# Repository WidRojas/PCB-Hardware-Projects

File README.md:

## [Variable Buck Converter(WIP)](./Buck/)

This project involved creating a buck converter which could regulate a 10V power supply to voltage suitable for a breadboard. simulations were done in LTspice and KiCad was used for creating schematics and PCB Layout.

### PCB Revision #1

*Currently awaiting second revision, due to high currents causing gate driver IC to fry*

## [LED Matrix](./Audio_Matrix/)

This project involved the creation of a LED matrix to be used in conjunction with audio [visualizer software](https://github.com/WidRojas/Audio_Visualiser), LED's are charlieplexed, STM32C071RBT6 was selected due to relatively low cost.

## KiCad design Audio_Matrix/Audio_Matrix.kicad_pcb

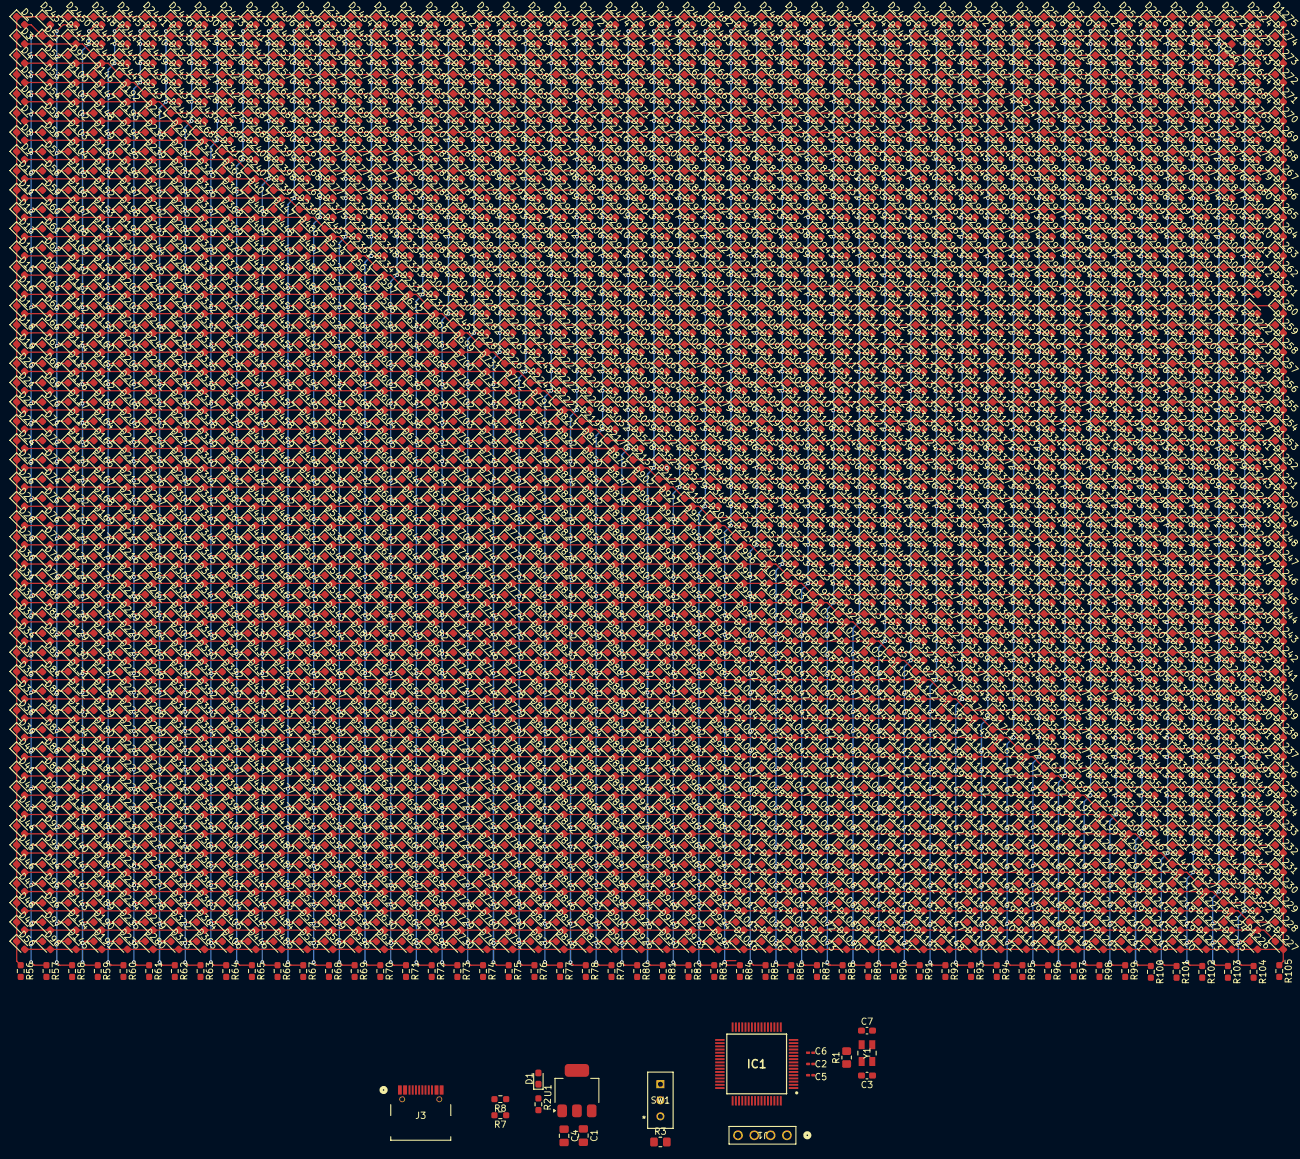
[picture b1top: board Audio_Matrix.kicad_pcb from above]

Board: 2 copper layers, 2519 parts (0 on the bottom side), 111 nets.

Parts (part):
C1, C4: 22u; C_0805_2012Metric_Pad1.18x1.45mm_HandSolder
C2, C5, C6: 100n; C_0201_0603Metric_Pad0.64x0.40mm_HandSolder
C3, C7: 10p; C_0603_1608Metric_Pad1.08x0.95mm_HandSolder
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
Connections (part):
+3.3V: C2.1, C4.1, C5.1, D1.2 (A), IC1.7 (VREF+), IC1.8 (VDD/VDDA), J1.4, SW1.1 (C), U1.2 (VO)
/CLK_IN: C3.1, IC1.10 (PF0-OSC_IN), Y1.1
/CLK_OUT: IC1.11 (PF1-OSC_OUT), R1.1
/LS1: D2.1 (K), D3.1 (K), D4.1 (K), D5.1 (K), D6.1 (K), D7.1 (K), D8.1 (K), D9.1 (K), D10.1 (K), D11.1 (K), D12.1 (K), D13.1 (K), D14.1 (K), D15.1 (K), D16.1 (K), D17.1 (K), D18.1 (K), D19.1 (K), D20.1 (K), D21.1 (K), D22.1 (K), D23.1 (K), D24.1 (K), D25.1 (K), D26.1 (K), D27.1 (K), D28.1 (K), D29.1 (K), D30.1 (K), D31.1 (K), D32.1 (K), D33.1 (K), D34.1 (K), D35.1 (K), D36.1 (K), D37.1 (K), D38.1 (K), D39.1 (K), D40.1 (K), D41.1 (K), D42.1 (K), D43.1 (K), D44.1 (K), D45.1 (K), D46.1 (K), D47.1 (K), D48.1 (K), D49.1 (K), D50.1 (K), D1275.1 (K), D2385.1 (K), D2396.1 (K), D2406.1 (K), D2415.1 (K), D2423.1 (K), D2430.1 (K), D2436.1 (K), D2441.1 (K), D2445.1 (K), D2448.1 (K), D2450.1 (K), D2451.1 (K), D2454.1 (K), D2456.1 (K), D2458.1 (K), D2460.1 (K), D2462.1 (K), D2464.1 (K), D2466.1 (K), D2468.1 (K), D2470.1 (K), D2472.1 (K), D2474.1 (K), D2476.1 (K), D2478.1 (K), D2480.1 (K), D2482.1 (K), D2484.1 (K), D2486.1 (K), D2488.1 (K), D2490.1 (K)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
/LS2: D2.2 (A), D51.1 (K), D52.1 (K), D53.1 (K), D54.1 (K), D55.1 (K), D56.1 (K), D57.1 (K), D58.1 (K), D59.1 (K), D60.1 (K), D61.1 (K), D62.1 (K), D63.1 (K), D64.1 (K), D65.1 (K), D66.1 (K), D67.1 (K), D68.1 (K), D69.1 (K), D70.1 (K), D71.1 (K), D72.1 (K), D73.1 (K), D74.1 (K), D75.1 (K), D76.1 (K), D77.1 (K), D78.1 (K), D79.1 (K), D80.1 (K), D81.1 (K), D82.1 (K), D83.1 (K), D84.1 (K), D85.1 (K), D86.1 (K), D87.1 (K), D88.1 (K), D89.1 (K), D90.1 (K), D91.1 (K), D92.1 (K), D93.1 (K), D94.1 (K), D95.1 (K), D96.1 (K), D97.1 (K), D98.1 (K), D1274.1 (K), D2384.1 (K), D2395.1 (K), D2405.1 (K), D2414.1 (K), D2422.1 (K), D2429.1 (K), D2435.1 (K), D2440.1 (K), D2444.1 (K), D2447.1 (K), D2449.1 (K), D2451.2 (A), D2455.1 (K), D2457.1 (K), D2459.1 (K), D2461.1 (K), D2463.1 (K), D2465.1 (K), D2467.1 (K), D2469.1 (K), D2471.1 (K), D2473.1 (K), D2475.1 (K), D2477.1 (K), D2479.1 (K), D2481.1 (K), D2483.1 (K), D2485.1 (K), D2487.1 (K), D2489.1 (K), D2491.1 (K)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
/LS3: D3.2 (A), D51.2 (A), D99.1 (K), D100.1 (K), D101.1 (K), D102.1 (K), D103.1 (K), D104.1 (K), D105.1 (K), D106.1 (K), D107.1 (K), D108.1 (K), D109.1 (K), D110.1 (K), D111.1 (K), D112.1 (K), D113.1 (K), D114.1 (K), D115.1 (K), D116.1 (K), D117.1 (K), D118.1 (K), D119.1 (K), D120.1 (K), D121.1 (K), D122.1 (K), D123.1 (K), D124.1 (K), D125.1 (K), D126.1 (K), D127.1 (K), D128.1 (K), D129.1 (K), D130.1 (K), D131.1 (K), D132.1 (K), D133.1 (K), D134.1 (K), D135.1 (K), D136.1 (K), D137.1 (K), D138.1 (K), D139.1 (K), D140.1 (K), D141.1 (K), D142.1 (K), D143.1 (K), D144.1 (K), D145.1 (K), D1273.1 (K), D2393.1 (K), D2421.1 (K), D2439.1 (K), D2443.1 (K), D2446.1 (K), D2449.2 (A), D2450.2 (A), D2526.1 (K), D2527.1 (K), D2528.1 (K), D2530.1 (K), D2531.1 (K), D2537.1 (K), D2538.1 (K), D2541.1 (K), D2544.1 (K), D2545.1 (K), D2546.1 (K), D2549.1 (K), D2550.1 (K), D2551.1 (K), D2553.1 (K), D2558.1 (K), D2560.1 (K), D2562.1 (K), D2566.1 (K), D2567.1 (K), D2573.1 (K), D2575.1 (K), D2577.1 (K), D2579.1 (K)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
/LS4: D4.2 (A), D52.2 (A), D99.2 (A), D146.1 (K), D147.1 (K), D148.1 (K), D149.1 (K), D150.1 (K), D151.1 (K), D152.1 (K), D153.1 (K), D154.1 (K), D155.1 (K), D156.1 (K), D157.1 (K), D158.1 (K), D159.1 (K), D160.1 (K), D161.1 (K), D162.1 (K), D163.1 (K), D164.1 (K), D165.1 (K), D166.1 (K), D167.1 (K), D168.1 (K), D169.1 (K), D170.1 (K), D171.1 (K), D172.1 (K), D173.1 (K), D174.1 (K), D175.1 (K), D176.1 (K), D177.1 (K), D178.1 (K), D179.1 (K), D180.1 (K), D181.1 (K), D182.1 (K), D183.1 (K), D184.1 (K), D185.1 (K), D186.1 (K), D187.1 (K), D188.1 (K), D189.1 (K), D190.1 (K), D191.1 (K), D1272.1 (K), D2420.1 (K), D2427.1 (K), D2433.1 (K), D2438.1 (K), D2442.1 (K), D2446.2 (A), D2447.2 (A), D2448.2 (A), D2569.1 (K), D2570.1 (K), D2571.1 (K), D2572.1 (K), D2574.1 (K), D2576.1 (K), D2578.1 (K), D2580.1 (K), D2582.1 (K), D2584.1 (K), D2586.1 (K), D2588.1 (K), D2590.1 (K), D2592.1 (K), D2594.1 (K), D2596.1 (K), D2598.1 (K), D2600.1 (K), D2602.1 (K), D2604.1 (K), D2606.1 (K), D2608.1 (K), D2610.1 (K)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
/LS5: D5.2 (A), D53.2 (A), D100.2 (A), D146.2 (A), D192.1 (K), D193.1 (K), D194.1 (K), D195.1 (K), D196.1 (K), D197.1 (K), D198.1 (K), D199.1 (K), D200.1 (K), D201.1 (K), D202.1 (K), D203.1 (K), D204.1 (K), D205.1 (K), D206.1 (K), D207.1 (K), D208.1 (K), D209.1 (K), D210.1 (K), D211.1 (K), D212.1 (K), D213.1 (K), D214.1 (K), D215.1 (K), D216.1 (K), D217.1 (K), D218.1 (K), D219.1 (K), D220.1 (K), D221.1 (K), D222.1 (K), D223.1 (K), D224.1 (K), D225.1 (K), D226.1 (K), D227.1 (K), D228.1 (K), D229.1 (K), D230.1 (K), D231.1 (K), D232.1 (K), D233.1 (K), D234.1 (K), D235.1 (K), D236.1 (K), D1271.1 (K), D2426.1 (K), D2428.1 (K), D2432.1 (K), D2437.1 (K), D2442.2 (A), D2443.2 (A), D2444.2 (A), D2445.2 (A), D2645.1 (K), D2646.1 (K), D2647.1 (K), D2648.1 (K), D2649.1 (K), D2650.1 (K), D2651.1 (K), D2652.1 (K), D2653.1 (K), D2654.1 (K), D2655.1 (K), D2656.1 (K), D2657.1 (K), D2658.1 (K), D2659.1 (K), D2660.1 (K), D2661.1 (K), D2662.1 (K), D2663.1 (K), D2664.1 (K), D2665.1 (K), D2666.1 (K), D2667.1 (K)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
/LS6: D6.2 (A), D54.2 (A), D101.2 (A), D147.2 (A), D192.2 (A), D237.1 (K), D238.1 (K), D239.1 (K), D240.1 (K), D241.1 (K), D242.1 (K), D243.1 (K), D244.1 (K), D245.1 (K), D246.1 (K), D247.1 (K), D248.1 (K), D249.1 (K), D250.1 (K), D251.1 (K), D252.1 (K), D253.1 (K), D254.1 (K), D255.1 (K), D256.1 (K), D257.1 (K), D258.1 (K), D259.1 (K), D260.1 (K), D261.1 (K), D262.1 (K), D263.1 (K), D264.1 (K), D265.1 (K), D266.1 (K), D267.1 (K), D268.1 (K), D269.1 (K), D270.1 (K), D271.1 (K), D272.1 (K), D273.1 (K), D274.1 (K), D275.1 (K), D276.1 (K), D277.1 (K), D278.1 (K), D279.1 (K), D280.1 (K), D1270.1 (K), D2424.1 (K), D2431.1 (K), D2434.1 (K), D2437.2 (A), D2438.2 (A), D2439.2 (A), D2440.2 (A), D2441.2 (A), D2687.1 (K), D2689.1 (K), D2691.1 (K), D2693.1 (K), D2695.1 (K), D2697.1 (K), D2699.1 (K), D2701.1 (K), D2703.1 (K), D2705.1 (K), D2707.1 (K), D2709.1 (K), D2711.1 (K), D2713.1 (K), D2715.1 (K), D2717.1 (K), D2719.1 (K), D2721.1 (K), D2723.1 (K), D2725.1 (K), D2727.1 (K), D2729.1 (K), D2731.1 (K)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
/LS7: D7.2 (A), D55.2 (A), D102.2 (A), D148.2 (A), D193.2 (A), D237.2 (A), D281.1 (K), D282.1 (K), D283.1 (K), D284.1 (K), D285.1 (K), D286.1 (K), D287.1 (K), D288.1 (K), D289.1 (K), D290.1 (K), D291.1 (K), D292.1 (K), D293.1 (K), D294.1 (K), D295.1 (K), D296.1 (K), D297.1 (K), D298.1 (K), D299.1 (K), D300.1 (K), D301.1 (K), D302.1 (K), D303.1 (K), D304.1 (K), D305.1 (K), D306.1 (K), D307.1 (K), D308.1 (K), D309.1 (K), D310.1 (K), D311.1 (K), D312.1 (K), D313.1 (K), D314.1 (K), D315.1 (K), D316.1 (K), D317.1 (K), D318.1 (K), D319.1 (K), D320.1 (K), D321.1 (K), D322.1 (K), D323.1 (K), D1269.1 (K), D2431.2 (A), D2432.2 (A), D2433.2 (A), D2435.2 (A), D2436.2 (A), D2526.2 (A), D2685.1 (K), D2686.1 (K), D2688.1 (K), D2690.1 (K), D2692.1 (K), D2694.1 (K), D2696.1 (K), D2698.1 (K), D2700.1 (K), D2702.1 (K), D2704.1 (K), D2706.1 (K), D2708.1 (K), D2710.1 (K), D2712.1 (K), D2714.1 (K), D2716.1 (K), D2718.1 (K), D2720.1 (K), D2722.1 (K), D2724.1 (K), D2726.1 (K), D2728.1 (K), D2730.1 (K), D2732.1 (K)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
/LS8: D8.2 (A), D56.2 (A), D103.2 (A), D149.2 (A), D194.2 (A), D238.2 (A), D281.2 (A), D324.1 (K), D325.1 (K), D326.1 (K), D327.1 (K), D328.1 (K), D329.1 (K), D330.1 (K), D331.1 (K), D332.1 (K), D333.1 (K), D334.1 (K), D335.1 (K), D336.1 (K), D337.1 (K), D338.1 (K), D339.1 (K), D340.1 (K), D341.1 (K), D342.1 (K), D343.1 (K), D344.1 (K), D345.1 (K), D346.1 (K), D347.1 (K), D348.1 (K), D349.1 (K), D350.1 (K), D351.1 (K), D352.1 (K), D353.1 (K), D354.1 (K), D355.1 (K), D356.1 (K), D357.1 (K), D358.1 (K), D359.1 (K), D360.1 (K), D361.1 (K), D362.1 (K), D363.1 (K), D364.1 (K), D365.1 (K), D1268.1 (K), D2399.1 (K), D2408.1 (K), D2416.1 (K), D2427.2 (A), D2428.2 (A), D2429.2 (A), D2430.2 (A), D2434.2 (A), D2527.2 (A), D2685.2 (A), D2767.1 (K), D2770.1 (K), D2773.1 (K), D2776.1 (K), D2779.1 (K), D2782.1 (K), D2785.1 (K), D2788.1 (K), D2791.1 (K), D2794.1 (K), D2797.1 (K), D2800.1 (K), D2803.1 (K), D2806.1 (K), D2809.1 (K), D2812.1 (K), D2815.1 (K), D2818.1 (K), D2821.1 (K), D2824.1 (K), D2827.1 (K)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
/LS9: D9.2 (A), D57.2 (A), D104.2 (A), D150.2 (A), D195.2 (A), D239.2 (A), D282.2 (A), D324.2 (A), D366.1 (K), D367.1 (K), D368.1 (K), D369.1 (K), D370.1 (K), D371.1 (K), D372.1 (K), D373.1 (K), D374.1 (K), D375.1 (K), D376.1 (K), D377.1 (K), D378.1 (K), D379.1 (K), D380.1 (K), D381.1 (K), D382.1 (K), D383.1 (K), D384.1 (K), D385.1 (K), D386.1 (K), D387.1 (K), D388.1 (K), D389.1 (K), D390.1 (K), D391.1 (K), D392.1 (K), D393.1 (K), D394.1 (K), D395.1 (K), D396.1 (K), D397.1 (K), D398.1 (K), D399.1 (K), D400.1 (K), D401.1 (K), D402.1 (K), D403.1 (K), D404.1 (K), D405.1 (K), D406.1 (K), D1267.1 (K), D2398.1 (K), D2407.1 (K), D2416.2 (A), D2420.2 (A), D2422.2 (A), D2423.2 (A), D2424.2 (A), D2426.2 (A), D2528.2 (A), D2686.2 (A), D2768.1 (K), D2771.1 (K), D2774.1 (K), D2777.1 (K), D2780.1 (K), D2783.1 (K), D2786.1 (K), D2789.1 (K), D2792.1 (K), D2795.1 (K), D2798.1 (K), D2801.1 (K), D2804.1 (K), D2807.1 (K), D2810.1 (K), D2813.1 (K), D2816.1 (K), D2819.1 (K), D2822.1 (K), D2825.1 (K), D2828.1 (K)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
/LS10: D10.2 (A), D58.2 (A), D105.2 (A), D151.2 (A), D196.2 (A), D240.2 (A), D283.2 (A), D325.2 (A), D366.2 (A), D407.1 (K), D408.1 (K), D409.1 (K), D410.1 (K), D411.1 (K), D412.1 (K), D413.1 (K), D414.1 (K), D415.1 (K), D416.1 (K), D417.1 (K), D418.1 (K), D419.1 (K), D420.1 (K), D421.1 (K), D422.1 (K), D423.1 (K), D424.1 (K), D425.1 (K), D426.1 (K), D427.1 (K), D428.1 (K), D429.1 (K), D430.1 (K), D431.1 (K), D432.1 (K), D433.1 (K), D434.1 (K), D435.1 (K), D436.1 (K), D437.1 (K), D438.1 (K), D439.1 (K), D440.1 (K), D441.1 (K), D442.1 (K), D443.1 (K), D444.1 (K), D445.1 (K), D446.1 (K), D1266.1 (K), D2397.1 (K), D2407.2 (A), D2408.2 (A), D2414.2 (A), D2415.2 (A), D2421.2 (A), D2569.2 (A), D2645.2 (A), D2687.2 (A), D2688.2 (A), D2769.1 (K), D2772.1 (K), D2775.1 (K), D2778.1 (K), D2781.1 (K), D2784.1 (K), D2787.1 (K), D2790.1 (K), D2793.1 (K), D2796.1 (K), D2799.1 (K), D2802.1 (K), D2805.1 (K), D2808.1 (K), D2811.1 (K), D2814.1 (K), D2817.1 (K), D2820.1 (K), D2823.1 (K), D2826.1 (K), D2829.1 (K)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
/LS11: D11.2 (A), D59.2 (A), D106.2 (A), D152.2 (A), D197.2 (A), D241.2 (A), D284.2 (A), D326.2 (A), D367.2 (A), D407.2 (A), D447.1 (K), D448.1 (K), D449.1 (K), D450.1 (K), D451.1 (K), D452.1 (K), D453.1 (K), D454.1 (K), D455.1 (K), D456.1 (K), D457.1 (K), D458.1 (K), D459.1 (K), D460.1 (K), D461.1 (K), D462.1 (K), D463.1 (K), D464.1 (K), D465.1 (K), D466.1 (K), D467.1 (K), D468.1 (K), D469.1 (K), D470.1 (K), D471.1 (K), D472.1 (K), D473.1 (K), D474.1 (K), D475.1 (K), D476.1 (K), D477.1 (K), D478.1 (K), D479.1 (K), D480.1 (K), D481.1 (K), D482.1 (K), D483.1 (K), D484.1 (K), D485.1 (K), D1265.1 (K), D2336.1 (K), D2350.1 (K), D2363.1 (K), D2375.1 (K), D2386.1 (K), D2397.2 (A), D2398.2 (A), D2399.2 (A), D2405.2 (A), D2406.2 (A), D2530.2 (A), D2570.2 (A), D2646.2 (A), D2689.2 (A), D2690.2 (A), D2881.1 (K), D2885.1 (K), D2889.1 (K), D2893.1 (K), D2897.1 (K), D2901.1 (K), D2905.1 (K), D2909.1 (K), D2913.1 (K), D2917.1 (K), D2921.1 (K), D2925.1 (K), D2929.1 (K), D2933.1 (K), D2937.1 (K), D2941.1 (K)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
/LS12: D12.2 (A), D60.2 (A), D107.2 (A), D153.2 (A), D198.2 (A), D242.2 (A), D285.2 (A), D327.2 (A), D368.2 (A), D408.2 (A), D447.2 (A), D486.1 (K), D487.1 (K), D488.1 (K), D489.1 (K), D490.1 (K), D491.1 (K), D492.1 (K), D493.1 (K), D494.1 (K), D495.1 (K), D496.1 (K), D497.1 (K), D498.1 (K), D499.1 (K), D500.1 (K), D501.1 (K), D502.1 (K), D503.1 (K), D504.1 (K), D505.1 (K), D506.1 (K), D507.1 (K), D508.1 (K), D509.1 (K), D510.1 (K), D511.1 (K), D512.1 (K), D513.1 (K), D514.1 (K), D515.1 (K), D516.1 (K), D517.1 (K), D518.1 (K), D519.1 (K), D520.1 (K), D521.1 (K), D522.1 (K), D523.1 (K), D1264.1 (K), D2335.1 (K), D2349.1 (K), D2362.1 (K), D2386.2 (A), D2395.2 (A), D2396.2 (A), D2452.1 (K), D2531.2 (A), D2571.2 (A), D2647.2 (A), D2691.2 (A), D2692.2 (A), D2767.2 (A), D2768.2 (A), D2769.2 (A), D2882.1 (K), D2886.1 (K), D2890.1 (K), D2894.1 (K), D2898.1 (K), D2902.1 (K), D2906.1 (K), D2910.1 (K), D2914.1 (K), D2918.1 (K), D2922.1 (K), D2926.1 (K), D2930.1 (K), D2934.1 (K), D2938.1 (K), D2942.1 (K)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
/LS13: D13.2 (A), D61.2 (A), D108.2 (A), D154.2 (A), D199.2 (A), D243.2 (A), D286.2 (A), D328.2 (A), D369.2 (A), D409.2 (A), D448.2 (A), D486.2 (A), D524.1 (K), D525.1 (K), D526.1 (K), D527.1 (K), D528.1 (K), D529.1 (K), D530.1 (K), D531.1 (K), D532.1 (K), D533.1 (K), D534.1 (K), D535.1 (K), D536.1 (K), D537.1 (K), D538.1 (K), D539.1 (K), D540.1 (K), D541.1 (K), D542.1 (K), D543.1 (K), D544.1 (K), D545.1 (K), D546.1 (K), D547.1 (K), D548.1 (K), D549.1 (K), D550.1 (K), D551.1 (K), D552.1 (K), D553.1 (K), D554.1 (K), D555.1 (K), D556.1 (K), D557.1 (K), D558.1 (K), D559.1 (K), D560.1 (K), D1263.1 (K), D2334.1 (K), D2348.1 (K), D2361.1 (K), D2375.2 (A), D2384.2 (A), D2385.2 (A), D2393.2 (A), D2452.2 (A), D2572.2 (A), D2648.2 (A), D2693.2 (A), D2694.2 (A), D2770.2 (A), D2771.2 (A), D2772.2 (A), D2883.1 (K), D2887.1 (K), D2891.1 (K), D2895.1 (K), D2899.1 (K), D2903.1 (K), D2907.1 (K), D2911.1 (K), D2915.1 (K), D2919.1 (K), D2923.1 (K), D2927.1 (K), D2931.1 (K), D2935.1 (K), D2939.1 (K), D2943.1 (K)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
/LS14: D14.2 (A), D62.2 (A), D109.2 (A), D155.2 (A), D200.2 (A), D244.2 (A), D287.2 (A), D329.2 (A), D370.2 (A), D410.2 (A), D449.2 (A), D487.2 (A), D524.2 (A), D561.1 (K), D562.1 (K), D563.1 (K), D564.1 (K), D565.1 (K), D566.1 (K), D567.1 (K), D568.1 (K), D569.1 (K), D570.1 (K), D571.1 (K), D572.1 (K), D573.1 (K), D574.1 (K), D575.1 (K), D576.1 (K), D577.1 (K), D578.1 (K), D579.1 (K), D580.1 (K), D581.1 (K), D582.1 (K), D583.1 (K), D584.1 (K), D585.1 (K), D586.1 (K), D587.1 (K), D588.1 (K), D589.1 (K), D590.1 (K), D591.1 (K), D592.1 (K), D593.1 (K), D594.1 (K), D595.1 (K), D596.1 (K), D1262.1 (K), D2333.1 (K), D2347.1 (K), D2361.2 (A), D2362.2 (A), D2363.2 (A), D2454.2 (A), D2455.2 (A), D2573.2 (A), D2574.2 (A), D2649.2 (A), D2695.2 (A), D2696.2 (A), D2773.2 (A), D2774.2 (A), D2775.2 (A), D2884.1 (K), D2888.1 (K), D2892.1 (K), D2896.1 (K), D2900.1 (K), D2904.1 (K), D2908.1 (K), D2912.1 (K), D2916.1 (K), D2920.1 (K), D2924.1 (K), D2928.1 (K), D2932.1 (K), D2936.1 (K), D2940.1 (K), D2944.1 (K)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
/LS15: D15.2 (A), D63.2 (A), D110.2 (A), D156.2 (A), D201.2 (A), D245.2 (A), D288.2 (A), D330.2 (A), D371.2 (A), D411.2 (A), D450.2 (A), D488.2 (A), D525.2 (A), D561.2 (A), D597.1 (K), D598.1 (K), D599.1 (K), D600.1 (K), D601.1 (K), D602.1 (K), D603.1 (K), D604.1 (K), D605.1 (K), D606.1 (K), D607.1 (K), D608.1 (K), D609.1 (K), D610.1 (K), D611.1 (K), D612.1 (K), D613.1 (K), D614.1 (K), D615.1 (K), D616.1 (K), D617.1 (K), D618.1 (K), D619.1 (K), D620.1 (K), D621.1 (K), D622.1 (K), D623.1 (K), D624.1 (K), D625.1 (K), D626.1 (K), D627.1 (K), D628.1 (K), D629.1 (K), D630.1 (K), D631.1 (K), D1261.1 (K), D2332.1 (K), D2347.2 (A), D2348.2 (A), D2349.2 (A), D2350.2 (A), D2456.2 (A), D2457.2 (A), D2575.2 (A), D2576.2 (A), D2650.2 (A), D2697.2 (A), D2698.2 (A), D2776.2 (A), D2777.2 (A), D2778.2 (A), D3013.1 (K), D3014.1 (K), D3015.1 (K), D3016.1 (K), D3017.1 (K), D3018.1 (K), D3019.1 (K), D3020.1 (K), D3021.1 (K), D3022.1 (K), D3023.1 (K), D3024.1 (K), D3025.1 (K), D3026.1 (K), D3027.1 (K), D3028.1 (K)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
/LS16: D16.2 (A), D64.2 (A), D111.2 (A), D157.2 (A), D202.2 (A), D246.2 (A), D289.2 (A), D331.2 (A), D372.2 (A), D412.2 (A), D451.2 (A), D489.2 (A), D526.2 (A), D562.2 (A), D597.2 (A), D632.1 (K), D633.1 (K), D634.1 (K), D635.1 (K), D636.1 (K), D637.1 (K), D638.1 (K), D639.1 (K), D640.1 (K), D641.1 (K), D642.1 (K), D643.1 (K), D644.1 (K), D645.1 (K), D646.1 (K), D647.1 (K), D648.1 (K), D649.1 (K), D650.1 (K), D651.1 (K), D652.1 (K), D653.1 (K), D654.1 (K), D655.1 (K), D656.1 (K), D657.1 (K), D658.1 (K), D659.1 (K), D660.1 (K), D661.1 (K), D662.1 (K), D663.1 (K), D664.1 (K), D665.1 (K), D1260.1 (K), D2205.1 (K), D2226.1 (K), D2246.1 (K), D2265.1 (K), D2283.1 (K), D2300.1 (K), D2316.1 (K), D2332.2 (A), D2333.2 (A), D2334.2 (A), D2335.2 (A), D2336.2 (A), D2458.2 (A), D2459.2 (A), D2577.2 (A), D2578.2 (A), D2651.2 (A), D2699.2 (A), D2700.2 (A), D2779.2 (A), D2780.2 (A), D2781.2 (A), D3046.1 (K), D3053.1 (K), D3060.1 (K), D3067.1 (K), D3074.1 (K), D3081.1 (K), D3088.1 (K), D3095.1 (K), D3102.1 (K)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
/LS17: D17.2 (A), D65.2 (A), D112.2 (A), D158.2 (A), D203.2 (A), D247.2 (A), D290.2 (A), D332.2 (A), D373.2 (A), D413.2 (A), D452.2 (A), D490.2 (A), D527.2 (A), D563.2 (A), D598.2 (A), D632.2 (A), D666.1 (K), D667.1 (K), D668.1 (K), D669.1 (K), D670.1 (K), D671.1 (K), D672.1 (K), D673.1 (K), D674.1 (K), D675.1 (K), D676.1 (K), D677.1 (K), D678.1 (K), D679.1 (K), D680.1 (K), D681.1 (K), D682.1 (K), D683.1 (K), D684.1 (K), D685.1 (K), D686.1 (K), D687.1 (K), D688.1 (K), D689.1 (K), D690.1 (K), D691.1 (K), D692.1 (K), D693.1 (K), D694.1 (K), D695.1 (K), D696.1 (K), D697.1 (K), D698.1 (K), D1259.1 (K), D2204.1 (K), D2225.1 (K), D2245.1 (K), D2264.1 (K), D2282.1 (K), D2316.2 (A), D2453.1 (K), D2460.2 (A), D2461.2 (A), D2579.2 (A), D2580.2 (A), D2652.2 (A), D2701.2 (A), D2702.2 (A), D2782.2 (A), D2783.2 (A), D2784.2 (A), D2881.2 (A), D2882.2 (A), D2883.2 (A), D2884.2 (A), D3013.2 (A), D3047.1 (K), D3054.1 (K), D3061.1 (K), D3068.1 (K), D3075.1 (K), D3082.1 (K), D3089.1 (K), D3096.1 (K), D3103.1 (K)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
/LS18: D18.2 (A), D66.2 (A), D113.2 (A), D159.2 (A), D204.2 (A), D248.2 (A), D291.2 (A), D333.2 (A), D374.2 (A), D414.2 (A), D453.2 (A), D491.2 (A), D528.2 (A), D564.2 (A), D599.2 (A), D633.2 (A), D666.2 (A), D699.1 (K), D700.1 (K), D701.1 (K), D702.1 (K), D703.1 (K), D704.1 (K), D705.1 (K), D706.1 (K), D707.1 (K), D708.1 (K), D709.1 (K), D710.1 (K), D711.1 (K), D712.1 (K), D713.1 (K), D714.1 (K), D715.1 (K), D716.1 (K), D717.1 (K), D718.1 (K), D719.1 (K), D720.1 (K), D721.1 (K), D722.1 (K), D723.1 (K), D724.1 (K), D725.1 (K), D726.1 (K), D727.1 (K), D728.1 (K), D729.1 (K), D730.1 (K), D1258.1 (K), D2203.1 (K), D2224.1 (K), D2244.1 (K), D2263.1 (K), D2281.1 (K), D2300.2 (A), D2453.2 (A), D2462.2 (A), D2463.2 (A), D2537.2 (A), D2582.2 (A), D2653.2 (A), D2703.2 (A), D2704.2 (A), D2785.2 (A), D2786.2 (A), D2787.2 (A), D2885.2 (A), D2886.2 (A), D2887.2 (A), D2888.2 (A), D3014.2 (A), D3048.1 (K), D3055.1 (K), D3062.1 (K), D3069.1 (K), D3076.1 (K), D3083.1 (K), D3090.1 (K), D3097.1 (K), D3104.1 (K)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
/LS19: D19.2 (A), D67.2 (A), D114.2 (A), D160.2 (A), D205.2 (A), D249.2 (A), D292.2 (A), D334.2 (A), D375.2 (A), D415.2 (A), D454.2 (A), D492.2 (A), D529.2 (A), D565.2 (A), D600.2 (A), D634.2 (A), D667.2 (A), D699.2 (A), D731.1 (K), D732.1 (K), D733.1 (K), D734.1 (K), D735.1 (K), D736.1 (K), D737.1 (K), D738.1 (K), D739.1 (K), D740.1 (K), D741.1 (K), D742.1 (K), D743.1 (K), D744.1 (K), D745.1 (K), D746.1 (K), D747.1 (K), D748.1 (K), D749.1 (K), D750.1 (K), D751.1 (K), D752.1 (K), D753.1 (K), D754.1 (K), D755.1 (K), D756.1 (K), D757.1 (K), D758.1 (K), D759.1 (K), D760.1 (K), D761.1 (K), D1257.1 (K), D2202.1 (K), D2223.1 (K), D2243.1 (K), D2262.1 (K), D2281.2 (A), D2282.2 (A), D2283.2 (A), D2464.2 (A), D2465.2 (A), D2538.2 (A), D2584.2 (A), D2654.2 (A), D2705.2 (A), D2706.2 (A), D2788.2 (A), D2789.2 (A), D2790.2 (A), D2889.2 (A), D2890.2 (A), D2891.2 (A), D2892.2 (A), D3015.2 (A), D3049.1 (K), D3056.1 (K), D3063.1 (K), D3070.1 (K), D3077.1 (K), D3084.1 (K), D3091.1 (K), D3098.1 (K), D3105.1 (K)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
/LS20: D20.2 (A), D68.2 (A), D115.2 (A), D161.2 (A), D206.2 (A), D250.2 (A), D293.2 (A), D335.2 (A), D376.2 (A), D416.2 (A), D455.2 (A), D493.2 (A), D530.2 (A), D566.2 (A), D601.2 (A), D635.2 (A), D668.2 (A), D700.2 (A), D731.2 (A), D762.1 (K), D763.1 (K), D764.1 (K), D765.1 (K), D766.1 (K), D767.1 (K), D768.1 (K), D769.1 (K), D770.1 (K), D771.1 (K), D772.1 (K), D773.1 (K), D774.1 (K), D775.1 (K), D776.1 (K), D777.1 (K), D778.1 (K), D779.1 (K), D780.1 (K), D781.1 (K), D782.1 (K), D783.1 (K), D784.1 (K), D785.1 (K), D786.1 (K), D787.1 (K), D788.1 (K), D789.1 (K), D790.1 (K), D791.1 (K), D1256.1 (K), D2201.1 (K), D2222.1 (K), D2242.1 (K), D2262.2 (A), D2263.2 (A), D2264.2 (A), D2265.2 (A), D2466.2 (A), D2467.2 (A), D2585.2 (A), D2586.2 (A), D2655.2 (A), D2707.2 (A), D2708.2 (A), D2791.2 (A), D2792.2 (A), D2793.2 (A), D2893.2 (A), D2894.2 (A), D2895.2 (A), D2896.2 (A), D3016.2 (A), D3050.1 (K), D3057.1 (K), D3064.1 (K), D3071.1 (K), D3078.1 (K), D3085.1 (K), D3092.1 (K), D3099.1 (K), D3106.1 (K)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
/LS21: D21.2 (A), D69.2 (A), D116.2 (A), D162.2 (A), D207.2 (A), D251.2 (A), D294.2 (A), D336.2 (A), D377.2 (A), D417.2 (A), D456.2 (A), D494.2 (A), D531.2 (A), D567.2 (A), D602.2 (A), D636.2 (A), D669.2 (A), D701.2 (A), D732.2 (A), D762.2 (A), D792.1 (K), D793.1 (K), D794.1 (K), D795.1 (K), D796.1 (K), D797.1 (K), D798.1 (K), D799.1 (K), D800.1 (K), D801.1 (K), D802.1 (K), D803.1 (K), D804.1 (K), D805.1 (K), D806.1 (K), D807.1 (K), D808.1 (K), D809.1 (K), D810.1 (K), D811.1 (K), D812.1 (K), D813.1 (K), D814.1 (K), D815.1 (K), D816.1 (K), D817.1 (K), D818.1 (K), D819.1 (K), D820.1 (K), D1255.1 (K), D2200.1 (K), D2221.1 (K), D2242.2 (A), D2243.2 (A), D2244.2 (A), D2245.2 (A), D2246.2 (A), D2468.2 (A), D2469.2 (A), D2587.2 (A), D2588.2 (A), D2656.2 (A), D2709.2 (A), D2710.2 (A), D2794.2 (A), D2795.2 (A), D2796.2 (A), D2897.2 (A), D2898.2 (A), D2899.2 (A), D2900.2 (A), D3017.2 (A), D3051.1 (K), D3058.1 (K), D3065.1 (K), D3072.1 (K), D3079.1 (K), D3086.1 (K), D3093.1 (K), D3100.1 (K), D3107.1 (K)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
/LS22: D22.2 (A), D70.2 (A), D117.2 (A), D163.2 (A), D208.2 (A), D252.2 (A), D295.2 (A), D337.2 (A), D378.2 (A), D418.2 (A), D457.2 (A), D495.2 (A), D532.2 (A), D568.2 (A), D603.2 (A), D637.2 (A), D670.2 (A), D702.2 (A), D733.2 (A), D763.2 (A), D792.2 (A), D821.1 (K), D822.1 (K), D823.1 (K), D824.1 (K), D825.1 (K), D826.1 (K), D827.1 (K), D828.1 (K), D829.1 (K), D830.1 (K), D831.1 (K), D832.1 (K), D833.1 (K), D834.1 (K), D835.1 (K), D836.1 (K), D837.1 (K), D838.1 (K), D839.1 (K), D840.1 (K), D841.1 (K), D842.1 (K), D843.1 (K), D844.1 (K), D845.1 (K), D846.1 (K), D847.1 (K), D848.1 (K), D1254.1 (K), D2199.1 (K), D2221.2 (A), D2222.2 (A), D2223.2 (A), D2224.2 (A), D2225.2 (A), D2226.2 (A), D2470.2 (A), D2471.2 (A), D2541.2 (A), D2590.2 (A), D2657.2 (A), D2711.2 (A), D2712.2 (A), D2797.2 (A), D2798.2 (A), D2799.2 (A), D2901.2 (A), D2902.2 (A), D2903.2 (A), D2904.2 (A), D3018.2 (A), D3052.1 (K), D3059.1 (K), D3066.1 (K), D3073.1 (K), D3080.1 (K), D3087.1 (K), D3094.1 (K), D3101.1 (K), D3108.1 (K)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
/LS23: D23.2 (A), D71.2 (A), D118.2 (A), D164.2 (A), D209.2 (A), D253.2 (A), D296.2 (A), D338.2 (A), D379.2 (A), D419.2 (A), D458.2 (A), D496.2 (A), D533.2 (A), D569.2 (A), D604.2 (A), D638.2 (A), D671.2 (A), D703.2 (A), D734.2 (A), D764.2 (A), D793.2 (A), D821.2 (A), D849.1 (K), D850.1 (K), D851.1 (K), D852.1 (K), D853.1 (K), D854.1 (K), D855.1 (K), D856.1 (K), D857.1 (K), D858.1 (K), D859.1 (K), D860.1 (K), D861.1 (K), D862.1 (K), D863.1 (K), D864.1 (K), D865.1 (K), D866.1 (K), D867.1 (K), D868.1 (K), D869.1 (K), D870.1 (K), D871.1 (K), D872.1 (K), D873.1 (K), D874.1 (K), D875.1 (K), D1253.1 (K), D2176.1 (K), D2199.2 (A), D2200.2 (A), D2201.2 (A), D2202.2 (A), D2203.2 (A), D2204.2 (A), D2205.2 (A), D2472.2 (A), D2473.2 (A), D2591.2 (A), D2592.2 (A), D2658.2 (A), D2713.2 (A), D2714.2 (A), D2800.2 (A), D2801.2 (A), D2802.2 (A), D2905.2 (A), D2906.2 (A), D2907.2 (A), D2908.2 (A), D3019.2 (A), D3228.1 (K), D3241.1 (K), D3254.1 (K), D3267.1 (K), D3280.1 (K), D3293.1 (K), D3306.1 (K), D3319.1 (K)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
/LS24: D24.2 (A), D72.2 (A), D119.2 (A), D165.2 (A), D210.2 (A), D254.2 (A), D297.2 (A), D339.2 (A), D380.2 (A), D420.2 (A), D459.2 (A), D497.2 (A), D534.2 (A), D570.2 (A), D605.2 (A), D639.2 (A), D672.2 (A), D704.2 (A), D735.2 (A), D765.2 (A), D794.2 (A), D822.2 (A), D849.2 (A), D876.1 (K), D877.1 (K), D878.1 (K), D879.1 (K), D880.1 (K), D881.1 (K), D882.1 (K), D883.1 (K), D884.1 (K), D885.1 (K), D886.1 (K), D887.1 (K), D888.1 (K), D889.1 (K), D890.1 (K), D891.1 (K), D892.1 (K), D893.1 (K), D894.1 (K), D895.1 (K), D896.1 (K), D897.1 (K), D898.1 (K), D899.1 (K), D900.1 (K), D901.1 (K), D1252.1 (K), D2152.1 (K), D2176.2 (A), D2474.2 (A), D2475.2 (A), D2593.2 (A), D2594.2 (A), D2659.2 (A), D2715.2 (A), D2716.2 (A), D2803.2 (A), D2804.2 (A), D2805.2 (A), D2909.2 (A), D2910.2 (A), D2911.2 (A), D2912.2 (A), D3020.2 (A), D3046.2 (A), D3047.2 (A), D3048.2 (A), D3049.2 (A), D3050.2 (A), D3051.2 (A), D3052.2 (A), D3229.1 (K), D3242.1 (K), D3255.1 (K), D3268.1 (K), D3281.1 (K), D3294.1 (K), D3307.1 (K)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
/LS25: D25.2 (A), D73.2 (A), D120.2 (A), D166.2 (A), D211.2 (A), D255.2 (A), D298.2 (A), D340.2 (A), D381.2 (A), D421.2 (A), D460.2 (A), D498.2 (A), D535.2 (A), D571.2 (A), D606.2 (A), D640.2 (A), D673.2 (A), D705.2 (A), D736.2 (A), D766.2 (A), D795.2 (A), D823.2 (A), D850.2 (A), D876.2 (A), D902.1 (K), D903.1 (K), D904.1 (K), D905.1 (K), D906.1 (K), D907.1 (K), D908.1 (K), D909.1 (K), D910.1 (K), D911.1 (K), D912.1 (K), D913.1 (K), D914.1 (K), D915.1 (K), D916.1 (K), D917.1 (K), D918.1 (K), D919.1 (K), D920.1 (K), D921.1 (K), D922.1 (K), D923.1 (K), D924.1 (K), D925.1 (K), D926.1 (K), D1251.1 (K), D2127.1 (K), D2152.2 (A), D2476.2 (A), D2477.2 (A), D2544.2 (A), D2596.2 (A), D2660.2 (A), D2717.2 (A), D2718.2 (A), D2806.2 (A), D2807.2 (A), D2808.2 (A), D2913.2 (A), D2914.2 (A), D2915.2 (A), D2916.2 (A), D3021.2 (A), D3053.2 (A), D3054.2 (A), D3055.2 (A), D3056.2 (A), D3057.2 (A), D3058.2 (A), D3059.2 (A), D3230.1 (K), D3243.1 (K), D3256.1 (K), D3269.1 (K), D3282.1 (K), D3295.1 (K), D3308.1 (K)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
/LS26: D26.2 (A), D74.2 (A), D121.2 (A), D167.2 (A), D212.2 (A), D256.2 (A), D299.2 (A), D341.2 (A), D382.2 (A), D422.2 (A), D461.2 (A), D499.2 (A), D536.2 (A), D572.2 (A), D607.2 (A), D641.2 (A), D674.2 (A), D706.2 (A), D737.2 (A), D767.2 (A), D796.2 (A), D824.2 (A), D851.2 (A), D877.2 (A), D902.2 (A), D927.1 (K), D928.1 (K), D929.1 (K), D930.1 (K), D931.1 (K), D932.1 (K), D933.1 (K), D934.1 (K), D935.1 (K), D936.1 (K), D937.1 (K), D938.1 (K), D939.1 (K), D940.1 (K), D941.1 (K), D942.1 (K), D943.1 (K), D944.1 (K), D945.1 (K), D946.1 (K), D947.1 (K), D948.1 (K), D949.1 (K), D950.1 (K), D1250.1 (K), D2101.1 (K), D2127.2 (A), D2478.2 (A), D2479.2 (A), D2545.2 (A), D2598.2 (A), D2661.2 (A), D2719.2 (A), D2720.2 (A), D2809.2 (A), D2810.2 (A), D2811.2 (A), D2917.2 (A), D2918.2 (A), D2919.2 (A), D2920.2 (A), D3022.2 (A), D3060.2 (A), D3061.2 (A), D3062.2 (A), D3063.2 (A), D3064.2 (A), D3065.2 (A), D3066.2 (A), D3231.1 (K), D3244.1 (K), D3257.1 (K), D3270.1 (K), D3283.1 (K), D3296.1 (K), D3309.1 (K)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
/LS27: D27.2 (A), D75.2 (A), D122.2 (A), D168.2 (A), D213.2 (A), D257.2 (A), D300.2 (A), D342.2 (A), D383.2 (A), D423.2 (A), D462.2 (A), D500.2 (A), D537.2 (A), D573.2 (A), D608.2 (A), D642.2 (A), D675.2 (A), D707.2 (A), D738.2 (A), D768.2 (A), D797.2 (A), D825.2 (A), D852.2 (A), D878.2 (A), D903.2 (A), D927.2 (A), D951.1 (K), D952.1 (K), D953.1 (K), D954.1 (K), D955.1 (K), D956.1 (K), D957.1 (K), D958.1 (K), D959.1 (K), D960.1 (K), D961.1 (K), D962.1 (K), D963.1 (K), D964.1 (K), D965.1 (K), D966.1 (K), D967.1 (K), D968.1 (K), D969.1 (K), D970.1 (K), D971.1 (K), D972.1 (K), D973.1 (K), D1249.1 (K), D2074.1 (K), D2101.2 (A), D2480.2 (A), D2481.2 (A), D2546.2 (A), D2600.2 (A), D2662.2 (A), D2721.2 (A), D2722.2 (A), D2812.2 (A), D2813.2 (A), D2814.2 (A), D2921.2 (A), D2922.2 (A), D2923.2 (A), D2924.2 (A), D3023.2 (A), D3067.2 (A), D3068.2 (A), D3069.2 (A), D3070.2 (A), D3071.2 (A), D3072.2 (A), D3073.2 (A), D3232.1 (K), D3245.1 (K), D3258.1 (K), D3271.1 (K), D3284.1 (K), D3297.1 (K), D3310.1 (K)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
/LS28: D28.2 (A), D76.2 (A), D123.2 (A), D169.2 (A), D214.2 (A), D258.2 (A), D301.2 (A), D343.2 (A), D384.2 (A), D424.2 (A), D463.2 (A), D501.2 (A), D538.2 (A), D574.2 (A), D609.2 (A), D643.2 (A), D676.2 (A), D708.2 (A), D739.2 (A), D769.2 (A), D798.2 (A), D826.2 (A), D853.2 (A), D879.2 (A), D904.2 (A), D928.2 (A), D951.2 (A), D974.1 (K), D975.1 (K), D976.1 (K), D977.1 (K), D978.1 (K), D979.1 (K), D980.1 (K), D981.1 (K), D982.1 (K), D983.1 (K), D984.1 (K), D985.1 (K), D986.1 (K), D987.1 (K), D988.1 (K), D989.1 (K), D990.1 (K), D991.1 (K), D992.1 (K), D993.1 (K), D994.1 (K), D995.1 (K), D1248.1 (K), D2046.1 (K), D2074.2 (A), D2482.2 (A), D2483.2 (A), D2601.2 (A), D2602.2 (A), D2663.2 (A), D2723.2 (A), D2724.2 (A), D2815.2 (A), D2816.2 (A), D2817.2 (A), D2925.2 (A), D2926.2 (A), D2927.2 (A), D2928.2 (A), D3024.2 (A), D3074.2 (A), D3075.2 (A), D3076.2 (A), D3077.2 (A), D3078.2 (A), D3079.2 (A), D3080.2 (A), D3233.1 (K), D3246.1 (K), D3259.1 (K), D3272.1 (K), D3285.1 (K), D3298.1 (K), D3311.1 (K)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
/LS29: D29.2 (A), D77.2 (A), D124.2 (A), D170.2 (A), D215.2 (A), D259.2 (A), D302.2 (A), D344.2 (A), D385.2 (A), D425.2 (A), D464.2 (A), D502.2 (A), D539.2 (A), D575.2 (A), D610.2 (A), D644.2 (A), D677.2 (A), D709.2 (A), D740.2 (A), D770.2 (A), D799.2 (A), D827.2 (A), D854.2 (A), D880.2 (A), D905.2 (A), D929.2 (A), D952.2 (A), D974.2 (A), D996.1 (K), D997.1 (K), D998.1 (K), D999.1 (K), D1000.1 (K), D1001.1 (K), D1002.1 (K), D1003.1 (K), D1004.1 (K), D1005.1 (K), D1006.1 (K), D1007.1 (K), D1008.1 (K), D1009.1 (K), D1010.1 (K), D1011.1 (K), D1012.1 (K), D1013.1 (K), D1014.1 (K), D1015.1 (K), D1016.1 (K), D1247.1 (K), D2017.1 (K), D2046.2 (A), D2484.2 (A), D2485.2 (A), D2603.2 (A), D2604.2 (A), D2664.2 (A), D2725.2 (A), D2726.2 (A), D2818.2 (A), D2819.2 (A), D2820.2 (A), D2929.2 (A), D2930.2 (A), D2931.2 (A), D2932.2 (A), D3025.2 (A), D3081.2 (A), D3082.2 (A), D3083.2 (A), D3084.2 (A), D3085.2 (A), D3086.2 (A), D3087.2 (A), D3234.1 (K), D3247.1 (K), D3260.1 (K), D3273.1 (K), D3286.1 (K), D3299.1 (K), D3312.1 (K)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
/LS30: D30.2 (A), D78.2 (A), D125.2 (A), D171.2 (A), D216.2 (A), D260.2 (A), D303.2 (A), D345.2 (A), D386.2 (A), D426.2 (A), D465.2 (A), D503.2 (A), D540.2 (A), D576.2 (A), D611.2 (A), D645.2 (A), D678.2 (A), D710.2 (A), D741.2 (A), D771.2 (A), D800.2 (A), D828.2 (A), D855.2 (A), D881.2 (A), D906.2 (A), D930.2 (A), D953.2 (A), D975.2 (A), D996.2 (A), D1017.1 (K), D1018.1 (K), D1019.1 (K), D1020.1 (K), D1021.1 (K), D1022.1 (K), D1023.1 (K), D1024.1 (K), D1025.1 (K), D1026.1 (K), D1027.1 (K), D1028.1 (K), D1029.1 (K), D1030.1 (K), D1031.1 (K), D1032.1 (K), D1033.1 (K), D1034.1 (K), D1035.1 (K), D1036.1 (K), D1246.1 (K), D1987.1 (K), D2017.2 (A), D2486.2 (A), D2487.2 (A), D2549.2 (A), D2606.2 (A), D2665.2 (A), D2727.2 (A), D2728.2 (A), D2821.2 (A), D2822.2 (A), D2823.2 (A), D2933.2 (A), D2934.2 (A), D2935.2 (A), D2936.2 (A), D3026.2 (A), D3088.2 (A), D3089.2 (A), D3090.2 (A), D3091.2 (A), D3092.2 (A), D3093.2 (A), D3094.2 (A), D3235.1 (K), D3248.1 (K), D3261.1 (K), D3274.1 (K), D3287.1 (K), D3300.1 (K), D3313.1 (K)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
/LS31: D31.2 (A), D79.2 (A), D126.2 (A), D172.2 (A), D217.2 (A), D261.2 (A), D304.2 (A), D346.2 (A), D387.2 (A), D427.2 (A), D466.2 (A), D504.2 (A), D541.2 (A), D577.2 (A), D612.2 (A), D646.2 (A), D679.2 (A), D711.2 (A), D742.2 (A), D772.2 (A), D801.2 (A), D829.2 (A), D856.2 (A), D882.2 (A), D907.2 (A), D931.2 (A), D954.2 (A), D976.2 (A), D997.2 (A), D1017.2 (A), D1037.1 (K), D1038.1 (K), D1039.1 (K), D1040.1 (K), D1041.1 (K), D1042.1 (K), D1043.1 (K), D1044.1 (K), D1045.1 (K), D1046.1 (K), D1047.1 (K), D1048.1 (K), D1049.1 (K), D1050.1 (K), D1051.1 (K), D1052.1 (K), D1053.1 (K), D1054.1 (K), D1055.1 (K), D1245.1 (K), D1956.1 (K), D1987.2 (A), D2488.2 (A), D2489.2 (A), D2550.2 (A), D2608.2 (A), D2666.2 (A), D2729.2 (A), D2730.2 (A), D2824.2 (A), D2825.2 (A), D2826.2 (A), D2937.2 (A), D2938.2 (A), D2939.2 (A), D2940.2 (A), D3027.2 (A), D3095.2 (A), D3096.2 (A), D3097.2 (A), D3098.2 (A), D3099.2 (A), D3100.2 (A), D3101.2 (A), D3236.1 (K), D3249.1 (K), D3262.1 (K), D3275.1 (K), D3288.1 (K), D3301.1 (K), D3314.1 (K)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
/LS32: D32.2 (A), D80.2 (A), D127.2 (A), D173.2 (A), D218.2 (A), D262.2 (A), D305.2 (A), D347.2 (A), D388.2 (A), D428.2 (A), D467.2 (A), D505.2 (A), D542.2 (A), D578.2 (A), D613.2 (A), D647.2 (A), D680.2 (A), D712.2 (A), D743.2 (A), D773.2 (A), D802.2 (A), D830.2 (A), D857.2 (A), D883.2 (A), D908.2 (A), D932.2 (A), D955.2 (A), D977.2 (A), D998.2 (A), D1018.2 (A), D1037.2 (A), D1056.1 (K), D1057.1 (K), D1058.1 (K), D1059.1 (K), D1060.1 (K), D1061.1 (K), D1062.1 (K), D1063.1 (K), D1064.1 (K), D1065.1 (K), D1066.1 (K), D1067.1 (K), D1068.1 (K), D1069.1 (K), D1070.1 (K), D1071.1 (K), D1072.1 (K), D1073.1 (K), D1244.1 (K), D1924.1 (K), D1956.2 (A), D2490.2 (A), D2491.2 (A), D2551.2 (A), D2610.2 (A), D2667.2 (A), D2731.2 (A), D2732.2 (A), D2827.2 (A), D2828.2 (A), D2829.2 (A), D2941.2 (A), D2942.2 (A), D2943.2 (A), D2944.2 (A), D3028.2 (A), D3102.2 (A), D3103.2 (A), D3104.2 (A), D3105.2 (A), D3106.2 (A), D3107.2 (A), D3108.2 (A), D3237.1 (K), D3250.1 (K), D3263.1 (K), D3276.1 (K), D3289.1 (K), D3302.1 (K), D3315.1 (K)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
/LS33: D33.2 (A), D81.2 (A), D128.2 (A), D174.2 (A), D219.2 (A), D263.2 (A), D306.2 (A), D348.2 (A), D389.2 (A), D429.2 (A), D468.2 (A), D506.2 (A), D543.2 (A), D579.2 (A), D614.2 (A), D648.2 (A), D681.2 (A), D713.2 (A), D744.2 (A), D774.2 (A), D803.2 (A), D831.2 (A), D858.2 (A), D884.2 (A), D909.2 (A), D933.2 (A), D956.2 (A), D978.2 (A), D999.2 (A), D1019.2 (A), D1038.2 (A), D1056.2 (A), D1074.1 (K), D1075.1 (K), D1076.1 (K), D1077.1 (K), D1078.1 (K), D1079.1 (K), D1080.1 (K), D1081.1 (K), D1082.1 (K), D1083.1 (K), D1084.1 (K), D1085.1 (K), D1086.1 (K), D1087.1 (K), D1088.1 (K), D1089.1 (K), D1090.1 (K), D1243.1 (K), D1891.1 (K), D1924.2 (A), D2492.2 (A), D2493.2 (A), D2611.2 (A), D2612.2 (A), D2668.2 (A), D2733.2 (A), D2734.2 (A), D2830.2 (A), D2831.2 (A), D2832.2 (A), D2945.2 (A), D2946.2 (A), D2947.2 (A), D2948.2 (A), D3029.2 (A), D3109.2 (A), D3110.2 (A), D3111.2 (A), D3112.2 (A), D3113.2 (A), D3114.2 (A), D3115.2 (A), D3238.1 (K), D3251.1 (K), D3264.1 (K), D3277.1 (K), D3290.1 (K), D3303.1 (K), D3316.1 (K)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
/LS34: D34.2 (A), D82.2 (A), D129.2 (A), D175.2 (A), D220.2 (A), D264.2 (A), D307.2 (A), D349.2 (A), D390.2 (A), D430.2 (A), D469.2 (A), D507.2 (A), D544.2 (A), D580.2 (A), D615.2 (A), D649.2 (A), D682.2 (A), D714.2 (A), D745.2 (A), D775.2 (A), D804.2 (A), D832.2 (A), D859.2 (A), D885.2 (A), D910.2 (A), D934.2 (A), D957.2 (A), D979.2 (A), D1000.2 (A), D1020.2 (A), D1039.2 (A), D1057.2 (A), D1074.2 (A), D1091.1 (K), D1092.1 (K), D1093.1 (K), D1094.1 (K), D1095.1 (K), D1096.1 (K), D1097.1 (K), D1098.1 (K), D1099.1 (K), D1100.1 (K), D1101.1 (K), D1102.1 (K), D1103.1 (K), D1104.1 (K), D1105.1 (K), D1106.1 (K), D1242.1 (K), D1857.1 (K), D1891.2 (A), D2494.2 (A), D2495.2 (A), D2553.2 (A), D2614.2 (A), D2669.2 (A), D2735.2 (A), D2736.2 (A), D2833.2 (A), D2834.2 (A), D2835.2 (A), D2949.2 (A), D2950.2 (A), D2951.2 (A), D2952.2 (A), D3030.2 (A), D3116.2 (A), D3117.2 (A), D3118.2 (A), D3119.2 (A), D3120.2 (A), D3121.2 (A), D3122.2 (A), D3239.1 (K), D3252.1 (K), D3265.1 (K), D3278.1 (K), D3291.1 (K), D3304.1 (K), D3317.1 (K)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
/LS35: D35.2 (A), D83.2 (A), D130.2 (A), D176.2 (A), D221.2 (A), D265.2 (A), D308.2 (A), D350.2 (A), D391.2 (A), D431.2 (A), D470.2 (A), D508.2 (A), D545.2 (A), D581.2 (A), D616.2 (A), D650.2 (A), D683.2 (A), D715.2 (A), D746.2 (A), D776.2 (A), D805.2 (A), D833.2 (A), D860.2 (A), D886.2 (A), D911.2 (A), D935.2 (A), D958.2 (A), D980.2 (A), D1001.2 (A), D1021.2 (A), D1040.2 (A), D1058.2 (A), D1075.2 (A), D1091.2 (A), D1107.1 (K), D1108.1 (K), D1109.1 (K), D1110.1 (K), D1111.1 (K), D1112.1 (K), D1113.1 (K), D1114.1 (K), D1115.1 (K), D1116.1 (K), D1117.1 (K), D1118.1 (K), D1119.1 (K), D1120.1 (K), D1121.1 (K), D1241.1 (K), D1822.1 (K), D1857.2 (A), D2496.2 (A), D2497.2 (A), D2615.2 (A), D2616.2 (A), D2670.2 (A), D2737.2 (A), D2738.2 (A), D2836.2 (A), D2837.2 (A), D2838.2 (A), D2953.2 (A), D2954.2 (A), D2955.2 (A), D2956.2 (A), D3031.2 (A), D3123.2 (A), D3124.2 (A), D3125.2 (A), D3126.2 (A), D3127.2 (A), D3128.2 (A), D3129.2 (A), D3240.1 (K), D3253.1 (K), D3266.1 (K), D3279.1 (K), D3292.1 (K), D3305.1 (K), D3318.1 (K)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
/LS36: D36.2 (A), D84.2 (A), D131.2 (A), D177.2 (A), D222.2 (A), D266.2 (A), D309.2 (A), D351.2 (A), D392.2 (A), D432.2 (A), D471.2 (A), D509.2 (A), D546.2 (A), D582.2 (A), D617.2 (A), D651.2 (A), D684.2 (A), D716.2 (A), D747.2 (A), D777.2 (A), D806.2 (A), D834.2 (A), D861.2 (A), D887.2 (A), D912.2 (A), D936.2 (A), D959.2 (A), D981.2 (A), D1002.2 (A), D1022.2 (A), D1041.2 (A), D1059.2 (A), D1076.2 (A), D1092.2 (A), D1107.2 (A), D1122.1 (K), D1123.1 (K), D1124.1 (K), D1125.1 (K), D1126.1 (K), D1127.1 (K), D1128.1 (K), D1129.1 (K), D1130.1 (K), D1131.1 (K), D1132.1 (K), D1133.1 (K), D1134.1 (K), D1135.1 (K), D1240.1 (K), D1786.1 (K), D1822.2 (A), D2498.2 (A), D2499.2 (A), D2617.2 (A), D2618.2 (A), D2671.2 (A), D2739.2 (A), D2740.2 (A), D2839.2 (A), D2840.2 (A), D2841.2 (A), D2957.2 (A), D2958.2 (A), D2959.2 (A), D2960.2 (A), D3032.2 (A), D3130.2 (A), D3131.2 (A), D3132.2 (A), D3133.2 (A), D3134.2 (A), D3135.2 (A), D3136.2 (A), D3384.1 (K), D3389.1 (K), D3394.1 (K), D3399.1 (K), D3404.1 (K), D3409.1 (K), D3424.2 (A)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
/LS37: D37.2 (A), D85.2 (A), D132.2 (A), D178.2 (A), D223.2 (A), D267.2 (A), D310.2 (A), D352.2 (A), D393.2 (A), D433.2 (A), D472.2 (A), D510.2 (A), D547.2 (A), D583.2 (A), D618.2 (A), D652.2 (A), D685.2 (A), D717.2 (A), D748.2 (A), D778.2 (A), D807.2 (A), D835.2 (A), D862.2 (A), D888.2 (A), D913.2 (A), D937.2 (A), D960.2 (A), D982.2 (A), D1003.2 (A), D1023.2 (A), D1042.2 (A), D1060.2 (A), D1077.2 (A), D1093.2 (A), D1108.2 (A), D1122.2 (A), D1136.1 (K), D1137.1 (K), D1138.1 (K), D1139.1 (K), D1140.1 (K), D1141.1 (K), D1142.1 (K), D1143.1 (K), D1144.1 (K), D1145.1 (K), D1146.1 (K), D1147.1 (K), D1148.1 (K), D1239.1 (K), D1749.1 (K), D1786.2 (A), D2500.2 (A), D2501.2 (A), D2619.2 (A), D2620.2 (A), D2672.2 (A), D2741.2 (A), D2742.2 (A), D2842.2 (A), D2843.2 (A), D2844.2 (A), D2961.2 (A), D2962.2 (A), D2963.2 (A), D2964.2 (A), D3033.2 (A), D3137.2 (A), D3138.2 (A), D3139.2 (A), D3140.2 (A), D3141.2 (A), D3142.2 (A), D3143.2 (A), D3385.1 (K), D3390.1 (K), D3395.1 (K), D3400.1 (K), D3405.1 (K), D3410.1 (K), D3429.2 (A)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
/LS38: D38.2 (A), D86.2 (A), D133.2 (A), D179.2 (A), D224.2 (A), D268.2 (A), D311.2 (A), D353.2 (A), D394.2 (A), D434.2 (A), D473.2 (A), D511.2 (A), D548.2 (A), D584.2 (A), D619.2 (A), D653.2 (A), D686.2 (A), D718.2 (A), D749.2 (A), D779.2 (A), D808.2 (A), D836.2 (A), D863.2 (A), D889.2 (A), D914.2 (A), D938.2 (A), D961.2 (A), D983.2 (A), D1004.2 (A), D1024.2 (A), D1043.2 (A), D1061.2 (A), D1078.2 (A), D1094.2 (A), D1109.2 (A), D1123.2 (A), D1136.2 (A), D1149.1 (K), D1150.1 (K), D1151.1 (K), D1152.1 (K), D1153.1 (K), D1154.1 (K), D1155.1 (K), D1156.1 (K), D1157.1 (K), D1158.1 (K), D1159.1 (K), D1160.1 (K), D1238.1 (K), D1711.1 (K), D1749.2 (A), D2502.2 (A), D2503.2 (A), D2621.2 (A), D2622.2 (A), D2673.2 (A), D2743.2 (A), D2744.2 (A), D2845.2 (A), D2846.2 (A), D2847.2 (A), D2965.2 (A), D2966.2 (A), D2967.2 (A), D2968.2 (A), D3034.2 (A), D3144.2 (A), D3145.2 (A), D3146.2 (A), D3147.2 (A), D3148.2 (A), D3149.2 (A), D3150.2 (A), D3358.2 (A), D3359.2 (A), D3360.2 (A), D3361.2 (A), D3362.2 (A), D3363.2 (A), D3364.2 (A)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
/LS39: D39.2 (A), D87.2 (A), D134.2 (A), D180.2 (A), D225.2 (A), D269.2 (A), D312.2 (A), D354.2 (A), D395.2 (A), D435.2 (A), D474.2 (A), D512.2 (A), D549.2 (A), D585.2 (A), D620.2 (A), D654.2 (A), D687.2 (A), D719.2 (A), D750.2 (A), D780.2 (A), D809.2 (A), D837.2 (A), D864.2 (A), D890.2 (A), D915.2 (A), D939.2 (A), D962.2 (A), D984.2 (A), D1005.2 (A), D1025.2 (A), D1044.2 (A), D1062.2 (A), D1079.2 (A), D1095.2 (A), D1110.2 (A), D1124.2 (A), D1137.2 (A), D1149.2 (A), D1161.1 (K), D1162.1 (K), D1163.1 (K), D1164.1 (K), D1165.1 (K), D1166.1 (K), D1167.1 (K), D1168.1 (K), D1169.1 (K), D1170.1 (K), D1171.1 (K), D1237.1 (K), D1672.1 (K), D1711.2 (A), D2504.2 (A), D2505.2 (A), D2558.2 (A), D2624.2 (A), D2674.2 (A), D2745.2 (A), D2746.2 (A), D2848.2 (A), D2849.2 (A), D2850.2 (A), D2969.2 (A), D2970.2 (A), D2971.2 (A), D2972.2 (A), D3035.2 (A), D3151.2 (A), D3152.2 (A), D3153.2 (A), D3154.2 (A), D3155.2 (A), D3156.2 (A), D3157.2 (A), D3371.2 (A), D3372.2 (A), D3373.2 (A), D3374.2 (A), D3375.2 (A), D3376.2 (A), D3377.2 (A)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
/LS40: D40.2 (A), D88.2 (A), D135.2 (A), D181.2 (A), D226.2 (A), D270.2 (A), D313.2 (A), D355.2 (A), D396.2 (A), D436.2 (A), D475.2 (A), D513.2 (A), D550.2 (A), D586.2 (A), D621.2 (A), D655.2 (A), D688.2 (A), D720.2 (A), D751.2 (A), D781.2 (A), D810.2 (A), D838.2 (A), D865.2 (A), D891.2 (A), D916.2 (A), D940.2 (A), D963.2 (A), D985.2 (A), D1006.2 (A), D1026.2 (A), D1045.2 (A), D1063.2 (A), D1080.2 (A), D1096.2 (A), D1111.2 (A), D1125.2 (A), D1138.2 (A), D1150.2 (A), D1161.2 (A), D1172.1 (K), D1173.1 (K), D1174.1 (K), D1175.1 (K), D1176.1 (K), D1177.1 (K), D1178.1 (K), D1179.1 (K), D1180.1 (K), D1181.1 (K), D1236.1 (K), D1632.1 (K), D1672.2 (A), D2506.2 (A), D2507.2 (A), D2625.2 (A), D2626.2 (A), D2675.2 (A), D2747.2 (A), D2748.2 (A), D2851.2 (A), D2852.2 (A), D2853.2 (A), D2973.2 (A), D2974.2 (A), D2975.2 (A), D2976.2 (A), D3036.2 (A), D3158.2 (A), D3159.2 (A), D3160.2 (A), D3161.2 (A), D3162.2 (A), D3163.2 (A), D3164.2 (A), D3332.2 (A), D3333.2 (A), D3334.2 (A), D3335.2 (A), D3336.2 (A), D3337.2 (A), D3338.2 (A)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
